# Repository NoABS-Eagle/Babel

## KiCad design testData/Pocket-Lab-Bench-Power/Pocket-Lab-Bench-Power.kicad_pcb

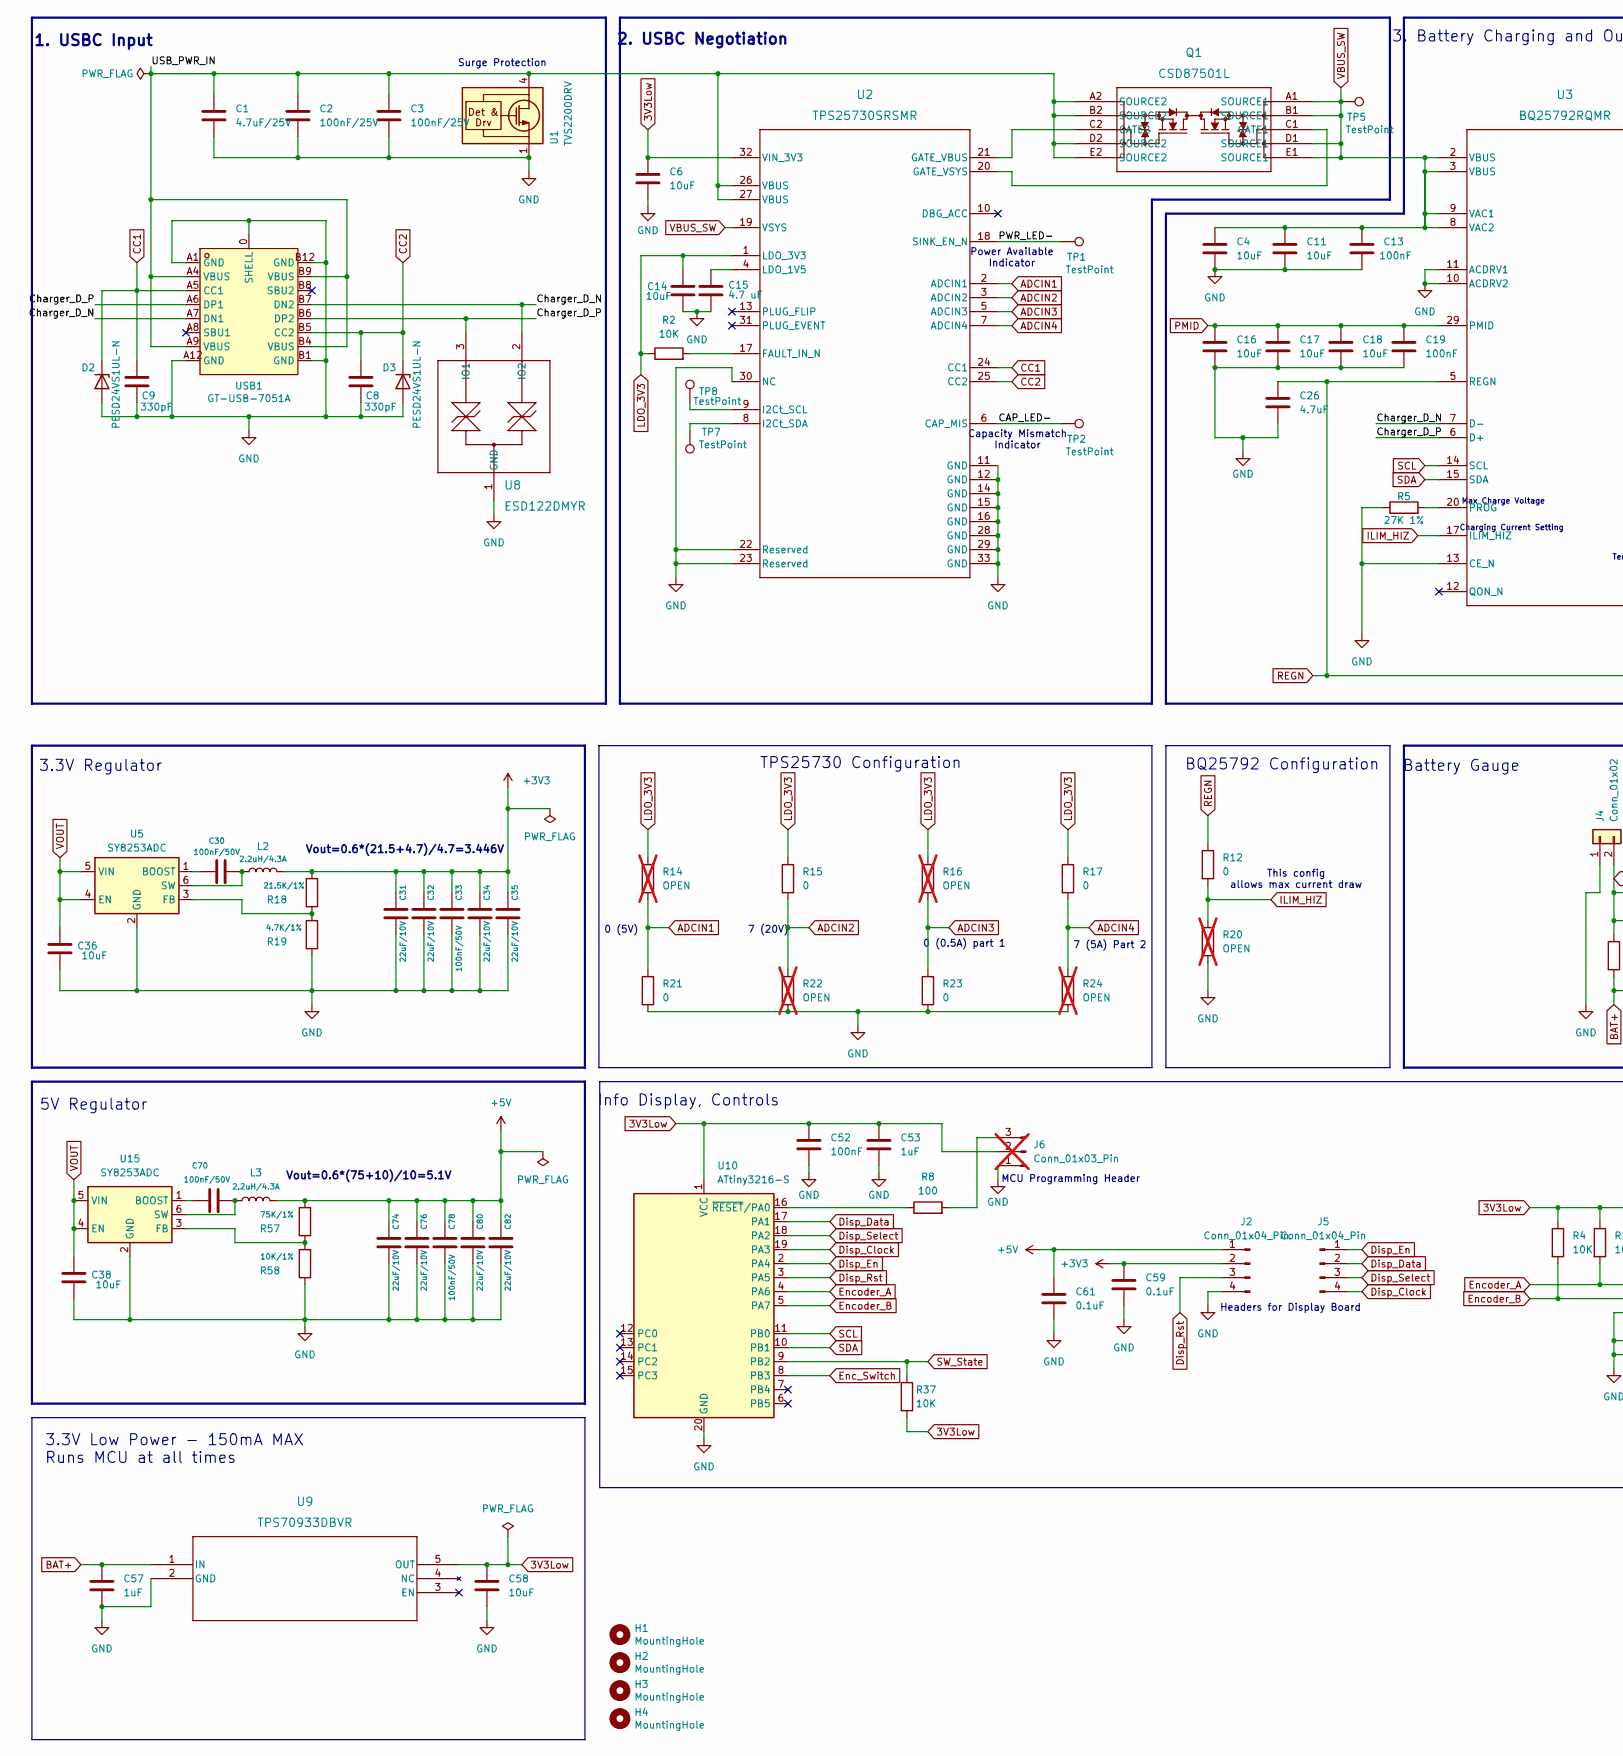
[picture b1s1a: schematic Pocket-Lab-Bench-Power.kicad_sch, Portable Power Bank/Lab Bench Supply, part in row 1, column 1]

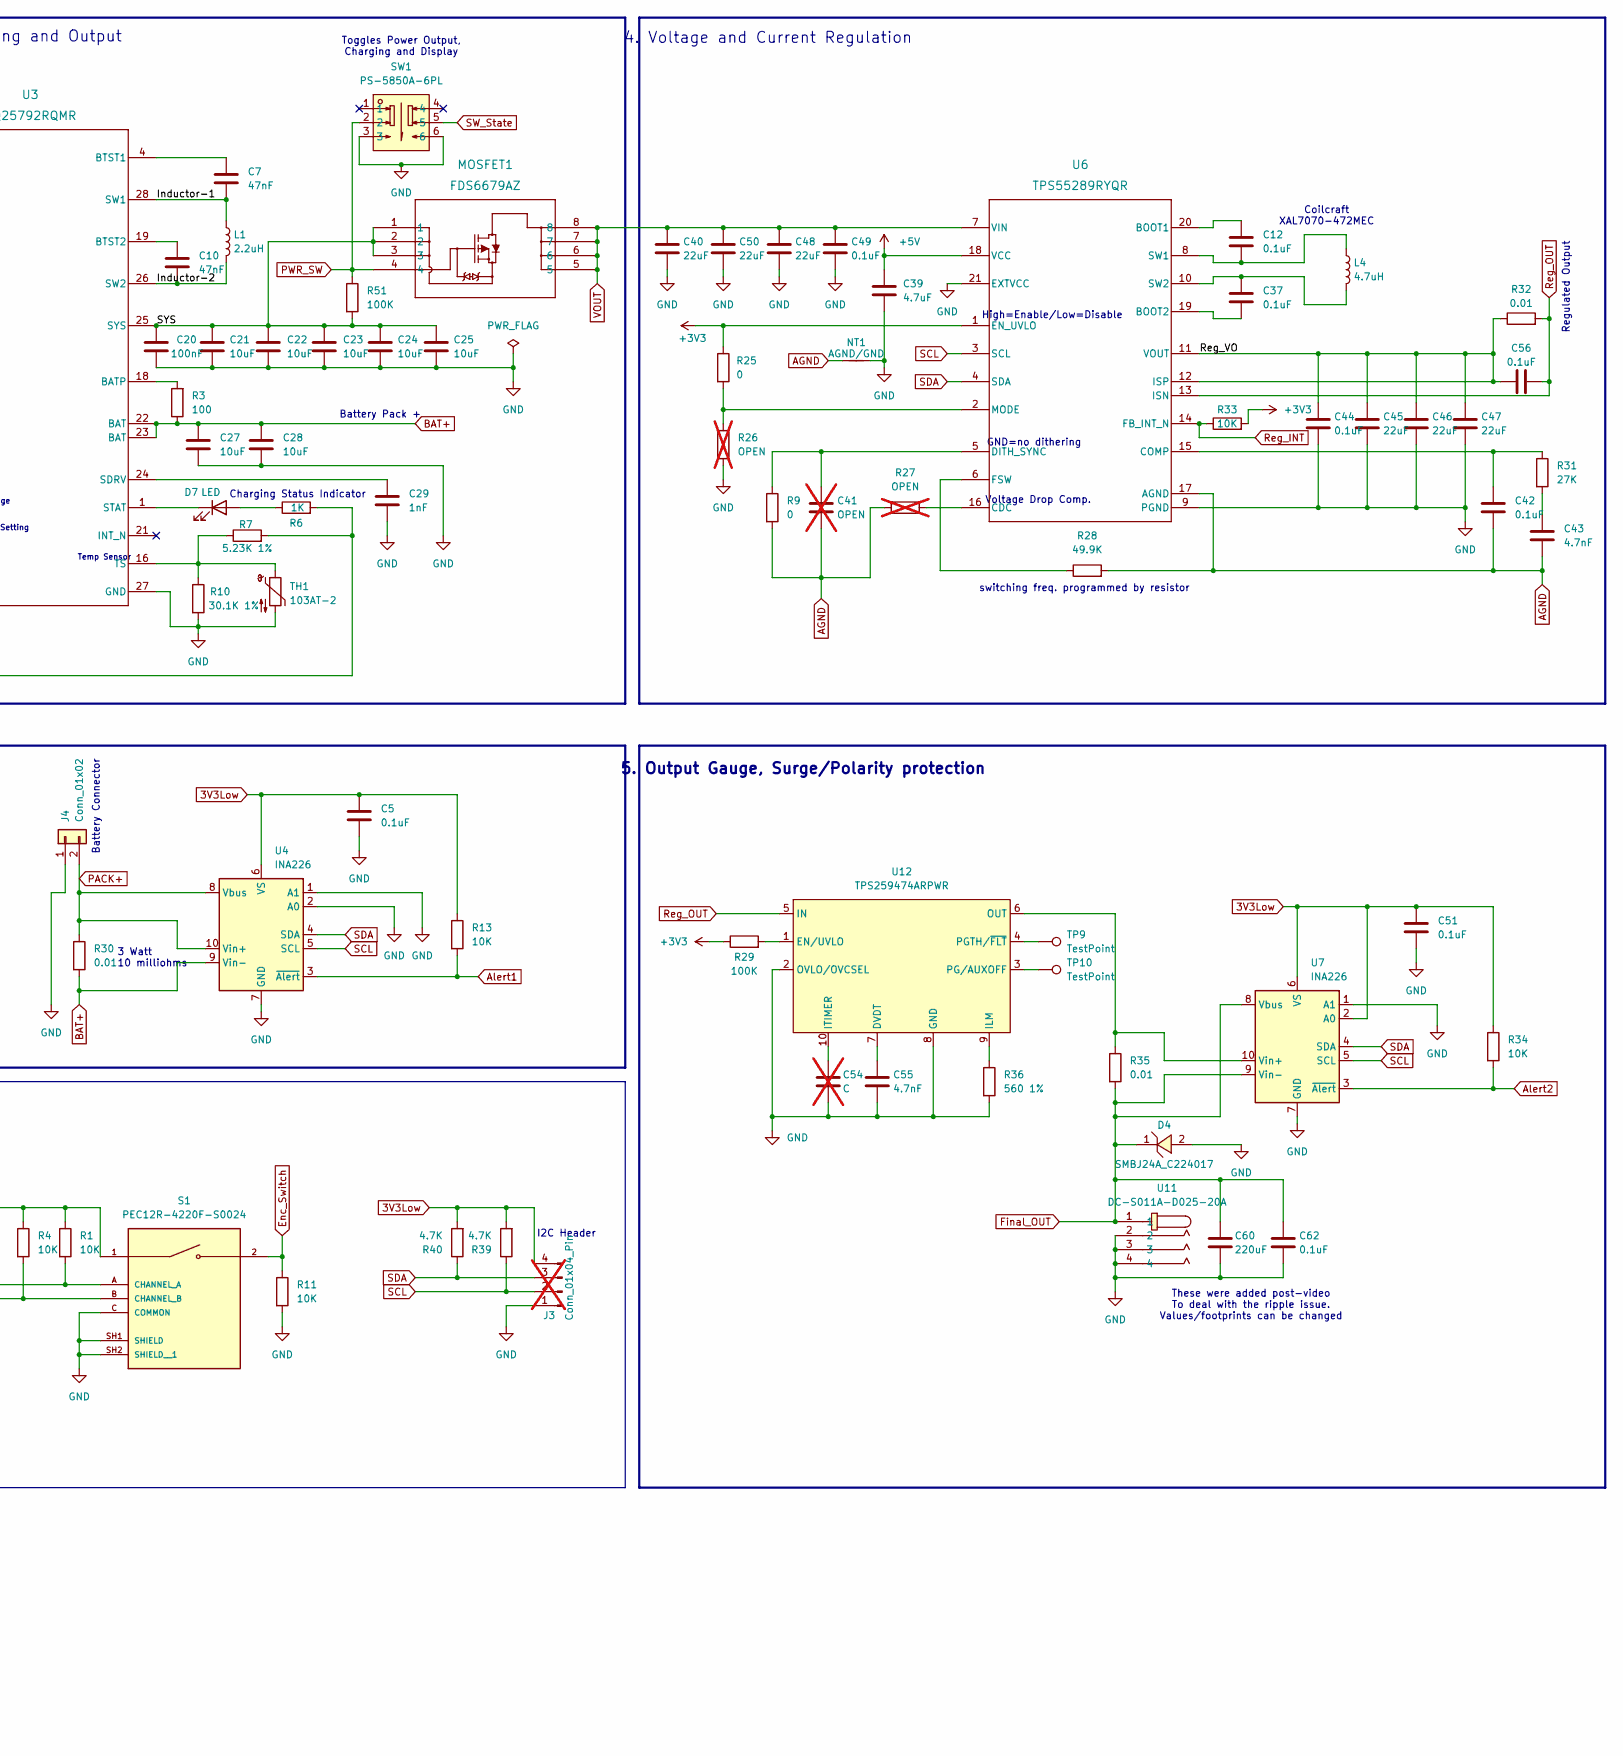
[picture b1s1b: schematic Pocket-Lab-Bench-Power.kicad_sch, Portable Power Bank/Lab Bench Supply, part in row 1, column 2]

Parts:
C1: 4.7uF/25V; C_0603_1608Metric
C2, C3: 100nF/25V; C_0603_1608Metric
C4, C11, C16, C17, C18, C21, C22, C23, C24, C25, C27, C28: 10uF; C_0805_2012Metric
C5, C12, C37, C42, C44, C49, C51, C56: 0.1uF; C_0402_1005Metric
C6, C14, C58: 10uF; C_0402_1005Metric
C7, C10: 47nF; C_0402_1005Metric
C8, C9: 330pF; C_0402_1005Metric
C13, C19, C20, C52: 100nF; C_0402_1005Metric
C15: 4.7 uF; C_0402_1005Metric
C26: 4.7uF; C_0603_1608Metric; Voltage Req 10V
C29: 1nF; C_0402_1005Metric
C30, C33, C70, C78: 100nF/50V; C_0603_1608Metric
C31, C32, C34, C35, C74, C76, C80, C82: 22uF/10V; C_0603_1608Metric
C36, C38: 10uF; C_0603_1608Metric
C39: 4.7uF; C_0603_1608Metric
C40, C45, C46, C47, C48, C50: 22uF; C_0603_1608Metric
C41: OPEN; C_0603_1608Metric; not fitted
C43: 4.7nF; C_0402_1005Metric
C53: 1uF; C_0402_1005Metric
C54: C; C_0603_1608Metric; not fitted
C55: 4.7nF; C_0603_1608Metric
C57: 1uF; C_0603_1608Metric
C59, C61, C62: 0.1uF; C_0603_1608Metric
C60: 220uF; C_0805_2012Metric
D2, D3: PESD24VS1UL-N; DFN1006-2L-RD; LCSC Part C406227
D4: SMBJ24A_C224017; SMB_L4.3-W3.6-LS5.4-RD; MPN SMBJ24A; LCSC Part C224017
D7: LED; LED_0603_1608Metric; LCSC Part C72038
H1, H2, H3, H4: MountingHole; MountingHole_3.2mm_M3
J2, J5: Conn_01x04_Pin; PinHeader_1x04_P2.54mm_Vertical; LCSC Part C2691448
J3: Conn_01x04_Pin; PinHeader_1x04_P2.54mm_Vertical; LCSC Part C2691448; not fitted
J4: Conn_01x02; JST_XH_B2B-XH-A_1x02_P2.50mm_Vertical; LCSC Part C495685
J6: Conn_01x03_Pin; PinHeader_1x03_P2.54mm_Vertical; LCSC Part C42431836; not fitted
L1: 2.2uH; IND-SMD_L7.0-W6.6_MCW-0650-220; LCSC Part C5349701
L2, L3: 2.2uH/4.3A; L_Sunlord_SWPA4020S; LCSC Part C3222957
L4: 4.7uH; IND-SMD_L7.5-W7.2-1; LCSC Part C3911513
MOSFET1: FDS6679AZ; SOIC8_751EB_ONS; LCSC Part C116730
NT1: AGND/GND; NetTie-2_SMD_Pad0.5mm
Q1: CSD87501L; PICOSTAR-YJG_TEX; LCSC Part C2841784
R1, R4, R11: 10K; R_0603_1608Metric
R2, R13, R33, R34, R37: 10K; R_0402_1005Metric
R3, R8: 100; R_0603_1608Metric
R5: 27K 1%; R_0603_1608Metric
R6: 1K; R_0603_1608Metric
R7: 5.23K 1%; R_0603_1608Metric
R9, R12, R15, R17, R21, R23, R25: 0; R_0603_1608Metric
R10: 30.1K 1%; R_0603_1608Metric
R14, R16, R20, R22, R24, R26, R27: OPEN; R_0603_1608Metric; not fitted
R18: 21.5K/1%; R_0603_1608Metric
R19: 4.7K/1%; R_0603_1608Metric
R28: 49.9K; R_0603_1608Metric
R29, R51: 100K; R_0603_1608Metric
R30, R32, R35: 0.01; R_2512_6332Metric; LCSC Part C840621
R31: 27K; R_0402_1005Metric
R36: 560 1%; R_0603_1608Metric
R39, R40: 4.7K; R_0603_1608Metric
R57: 75K/1%; R_0603_1608Metric
R58: 10K/1%; R_0603_1608Metric
S1: PEC12R-4220F-S0024; XDCR_PEC12R-4220F-S0024; PARTREV 07/21; LCSC Part C18164805
SW1: PS-5850A-6PL; SW-TH_6P-L5.8-W5.8-P2.00-LS4.5-BL_1; MPN PS-5850A-6PL; LCSC Part C963201
TH1: 103AT-2; PinHeader_1x02_P2.54mm_Vertical
TP1, TP2, TP5, TP7, TP8, TP9, TP10: TestPoint; TestPoint_Pad_D1.5mm
U1: TVS2200DRV; WSON-6-1EP_2x2mm_P0.65mm_EP1x1.6mm; LCSC Part C523793
U2: TPS25730SRSMR; RSM0032B-IPC_A; LCSC Part C22390380
U3: BQ25792RQMR; BQ25792; LCSC Part C2862876
U4: INA226; VSSOP-10_3x3mm_P0.5mm
U5, U15: SY8253ADC; TSOT-23-6; LCSC Part C93736
U6: TPS55289RYQR; RYQ0021A-MFG; LCSC Part C5942077
U7: INA226; VSSOP-10_3x3mm_P0.5mm; LCSC Part C49851
U8: ESD122DMYR; DMY0003A; LCSC Part C1975871
U9: TPS70933DBVR; DBV5_TEX; LCSC Part C89347
U10: ATtiny3216-S; SOIC-20W_7.5x12.8mm_P1.27mm; LCSC Part C1340355
U11: DC-S011A-D025-20A; AUDIO-TH_DC-S011A-D025-20A; MPN DC-S011A-D025-20A; LCSC Part C7464915
U12: TPS259474ARPWR; VQFN-10_L2.0-W2.0-P0.45-TL; MPN TPS259474ARPWR; LCSC Part C3662807
USB1: GT-USB-7051A; USB-C-SMD_GT-USB-7051A; MPN GT-USB-7051A; LCSC Part C2843970

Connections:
3V3Low: C5.1, C6.1, C51.1, C52.1, C53.1, C58.1, J3.4, J6.2, R1.1, R4.1, R13.1, R34.1, R37.2, R39.2, R40.2, S1.1, U2.32 (VIN_3V3), U4.6 (VS), U7.2 (A0), U7.6 (VS), U9.5 (OUT), U10.1 (VCC)
+3V3: C31.2, C32.2, C33.1, C34.2, C35.2, C59.1, J2.2, L2.2, R18.2, R25.1, R29.1, R33.2, U6.1 (EN_UVLO)
+5V: C39.1, C61.1, C74.2, C76.2, C78.1, C80.2, C82.2, J2.1, L3.2, R57.2, U6.18 (VCC)
/CAP_LED-: TP2.1, U2.6 (CAP_MIS)
/Charger_D_N: U3.7 (D-), U8.2 (IO2), USB1.A7 (DN1), USB1.B7 (DN2)
/Charger_D_P: U3.6 (D+), U8.3 (IO1), USB1.A6 (DP1), USB1.B6 (DP2)
/Inductor-1: C7.2, L1.1, U3.28 (SW1)
/Inductor-2: C10.2, L1.2, U3.26 (SW2)
/PWR_LED-: TP1.1, U2.18 (SINK_EN_N)
/Reg_VO: C44.1, C45.1, C46.1, C47.1, C56.1, R32.1, U6.11 (VOUT), U6.12 (ISP)
/SYS: C20.1, C21.1, C22.1, C23.1, C24.1, C25.1, MOSFET1.1, MOSFET1.2, MOSFET1.3, R51.2, U3.25 (SYS)
/USB_PWR_IN: C1.1, C2.1, C3.1, Q1.A2 (SOURCE2), Q1.B2 (SOURCE2), Q1.D2 (SOURCE2), Q1.E2 (SOURCE2), U1.4 (IN), U1.5 (IN), U1.6 (IN), U2.26 (VBUS), U2.27 (VBUS), USB1.A4 (VBUS), USB1.A9 (VBUS), USB1.B4 (VBUS), USB1.B9 (VBUS)
ADCIN1: R14.2, R21.1, U2.2 (ADCIN1)
ADCIN2: R15.2, R22.1, U2.3 (ADCIN2)
ADCIN3: R16.2, R23.1, U2.5 (ADCIN3)
ADCIN4: R17.2, R24.1, U2.7 (ADCIN4)
AGND: C41.2, C42.2, C43.2, NT1.1, R9.2, R27.1, R28.2, U6.17 (AGND)
Alert1: R13.2, U4.3 (~Alert)
Alert2: R34.2, U7.3 (~Alert)
BAT+: C27.1, C28.1, C57.1, R3.1, R30.2, U3.22 (BAT), U3.23 (BAT), U4.9 (Vin-), U9.1 (IN)
CC1: C9.1, D2.1 (K), U2.24 (CC1), USB1.A5 (CC1)
CC2: C8.1, D3.1 (K), U2.25 (CC2), USB1.B5 (CC2)
Disp_Clock: J5.4, U10.19 (PA3)
Disp_Data: J5.2, U10.17 (PA1)
Disp_En: J5.1, U10.2 (PA4)
Disp_Rst: J2.3, U10.3 (PA5)
Disp_Select: J5.3, U10.18 (PA2)
Enc_Switch: R11.1, S1.2, U10.8 (PB3)
Encoder_A: R1.2, S1.A (CHANNEL_A), U10.4 (PA6)
Encoder_B: R4.2, S1.B (CHANNEL_B), U10.5 (PA7)
Final_OUT: C60.1, C62.1, D4.1, R35.2, U7.8 (Vbus), U7.9 (Vin-), U11.1
GND: C1.2, C2.2, C3.2, C4.1, C5.2, C6.2, C8.2, C9.2, C11.1, C13.2, C14.2, C15.2, C16.2, C17.2, C18.1, C19.2, C20.2, C21.2, C22.2, C23.2, C24.2, C25.2, C26.2, C27.2, C28.2, C29.2, C31.1, C32.1, C33.2, C34.1, C35.1, C36.2, C38.2, C39.2, C40.2, C44.2, C45.2, C46.2, C47.2, C48.2, C49.2, C50.2, C51.2, C52.2, C53.2, C54.2, C55.2, C57.2, C58.2, C59.2, C60.2, C61.2, C62.2, C74.1, C76.1, C78.2, C80.1, C82.1, D2.2 (A), D3.2 (A), D4.2, J2.4, J3.1, J4.1, J6.1, NT1.2, R5.1, R10.2, R11.2, R19.1, R20.2, R21.2, R22.2, R23.2, R24.2, R26.2, R36.2, R58.1, S1.C (COMMON), S1.SH1 (SHIELD), S1.SH2 (SHIELD__1), SW1.3, SW1.6, TH1.2, U1.1 (GND), U1.2 (GND), U1.3 (GND), U1.7 (GND), U2.11 (GND), U2.12 (GND), U2.14 (GND), U2.15 (GND), U2.16 (GND), U2.22 (Reserved), U2.23 (Reserved), U2.28 (GND), U2.29 (GND), U2.30 (NC), U2.33 (GND), U3.10 (ACDRV2), U3.11 (ACDRV1), U3.13 (CE_N), U3.27 (GND), U4.1 (A1), U4.2 (A0), U4.7 (GND), U5.2 (GND), U6.9 (PGND), U6.21 (EXTVCC), U7.1 (A1), U7.7 (GND), U8.1 (GND), U9.2 (GND), U10.20 (GND), U11.2, U11.3, U11.4, U12.2 (OVLO/OVCSEL), U12.8 (GND), U15.2 (GND), USB1.0 (SHELL), USB1.A1 (GND), USB1.A12 (GND), USB1.B1 (GND), USB1.B12 (GND)
ILIM_HIZ: R12.2, R20.1, U3.17 (ILIM_HIZ)
LDO_3V3: C14.1, R2.1, R14.1, R15.1, R16.1, R17.1, U2.1 (LDO_3V3)
unnamed: C43.1, R31.2
unnamed: D7.2 (A), R6.1
unnamed: D7.1 (K), U3.1 (STAT)
unnamed: J6.3, R8.2
unnamed: Q1.C1 (GATE1), U2.20 (GATE_VSYS)
unnamed: Q1.C2 (GATE2), U2.21 (GATE_VBUS)
unnamed: R2.2, U2.17 (FAULT_IN_N)
unnamed: TP8.1, U2.9 (I2Ct_SCL)
unnamed: TP7.1, U2.8 (I2Ct_SDA)
unnamed: C15.1, U2.4 (LDO_1V5)
unnamed: R3.2, U3.18 (BATP)
unnamed: C7.1, U3.4 (BTST1)
unnamed: C10.1, U3.19 (BTST2)
unnamed: R5.2, U3.20 (PROG)
unnamed: C29.1, U3.24 (SDRV)
unnamed: R7.1, R10.1, TH1.1, U3.16 (TS)
unnamed: C30.2, U5.1 (BOOST)
unnamed: R18.1, R19.2, U5.3 (FB)
unnamed: C30.1, L2.1, U5.6 (SW)
unnamed: C12.1, U6.20 (BOOT1)
unnamed: C37.2, U6.19 (BOOT2)
unnamed: R27.2, U6.16 (CDC)
unnamed: C42.1, R31.1, U6.15 (COMP)
unnamed: C41.1, R9.1, U6.5 (DITH_SYNC)
unnamed: R28.1, U6.6 (FSW)
unnamed: R25.2, R26.1, U6.2 (MODE)
unnamed: C12.2, L4.1, U6.8 (SW1)
unnamed: C37.1, L4.2, U6.10 (SW2)
unnamed: R8.1, U10.16 (~RESET/PA0)
unnamed: C55.1, U12.7 (DVDT)
unnamed: R29.2, U12.1 (EN/UVLO)
unnamed: R36.1, U12.9 (ILM)
unnamed: C54.1, U12.10 (ITIMER)
unnamed: R35.1, U7.10 (Vin+), U12.6 (OUT)
unnamed: TP9.1, U12.4 (PGTH/~FLT)
unnamed: TP10.1, U12.3 (PG/AUXOFF)
unnamed: C70.2, U15.1 (BOOST)
unnamed: R57.1, R58.2, U15.3 (FB)
unnamed: C70.1, L3.1, U15.6 (SW)
PACK+: J4.2, R30.1, U4.8 (Vbus), U4.10 (Vin+)
PMID: C16.1, C17.1, C18.2, C19.1, U3.29 (PMID)
PWR_SW: MOSFET1.4, R51.1, SW1.2
REGN: C26.1, R6.2, R7.2, R12.1, U3.5 (REGN)
Reg_INT: R33.1, U6.14 (FB_INT_N)
Reg_OUT: C56.2, R32.2, U6.13 (ISN), U12.5 (IN)
SCL: J3.2, R39.1, U3.14 (SCL), U4.5 (SCL), U6.3 (SCL), U7.5 (SCL), U10.11 (PB0)
SDA: J3.3, R40.1, U3.15 (SDA), U4.4 (SDA), U6.4 (SDA), U7.4 (SDA), U10.10 (PB1)
SW_State: R37.1, SW1.5, U10.9 (PB2)
VBUS_SW: C4.2, C11.2, C13.1, Q1.A1 (SOURCE1), Q1.B1 (SOURCE1), Q1.D1 (SOURCE1), Q1.E1 (SOURCE1), TP5.1, U2.19 (VSYS), U3.2 (VBUS), U3.3 (VBUS), U3.8 (VAC2), U3.9 (VAC1)
VOUT: C36.1, C38.1, C40.1, C48.1, C49.1, C50.1, MOSFET1.5, MOSFET1.6, MOSFET1.7, MOSFET1.8, U5.4 (EN), U5.5 (VIN), U6.7 (VIN), U15.4 (EN), U15.5 (VIN)

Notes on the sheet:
Info Display, Controls
GND=no dithering
Battery Connector
4. Voltage and Current Regulation
Surge Protection
Voltage Drop Comp.
0 (5V)
switching freq. programmed by resistor
Battery Pack +
Charging Status Indicator
7 (20V)
BQ25792 Configuration
I2C Header
Temp Sensor
3.3V Regulator
Headers for Display Board
Coilcraft XAL7070-472MEC
1. USBC Input
2. USBC Negotiation
TPS25730 Configuration
5. Output Gauge, Surge/Polarity protection
Regulated Output
3.3V Low Power - 150mA MAX Runs MCU at all times
3. Battery Charging and Output
7 (5A) Part 2
0 (0.5A) part 1
Capacity Mismatch Indicator
Charging Current Setting
These were added post-video To deal with the ripple issue. Values/footprints can be changed
Power Available Indicator
MCU Programming Header
This config allows max current draw
Toggles Power Output, Charging and Display
3 Watt 10 milliohms
Max Charge Voltage
5V Regulator
Vout=0.6*(21.5+4.7)/4.7=3.446V
High=Enable/Low=Disable
Battery Gauge
Vout=0.6*(75+10)/10=5.1V

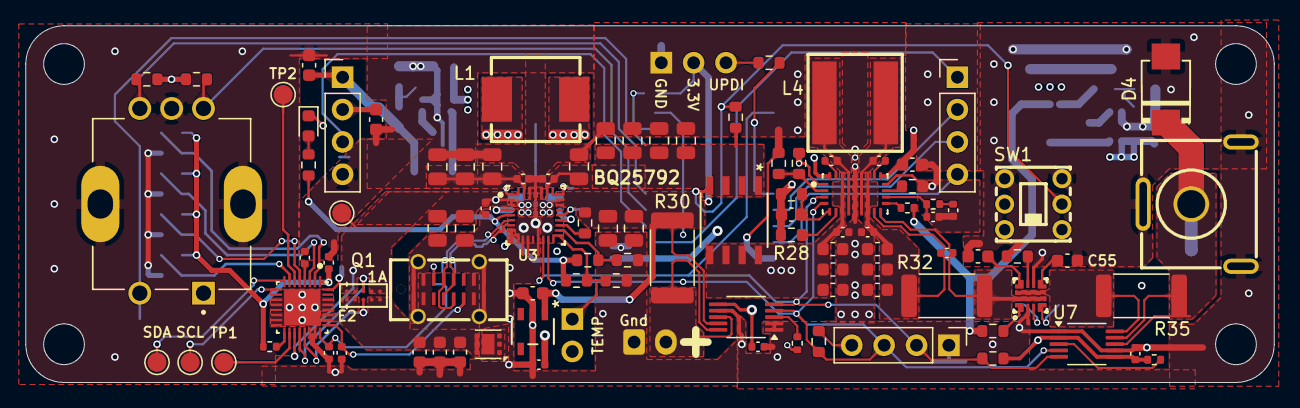
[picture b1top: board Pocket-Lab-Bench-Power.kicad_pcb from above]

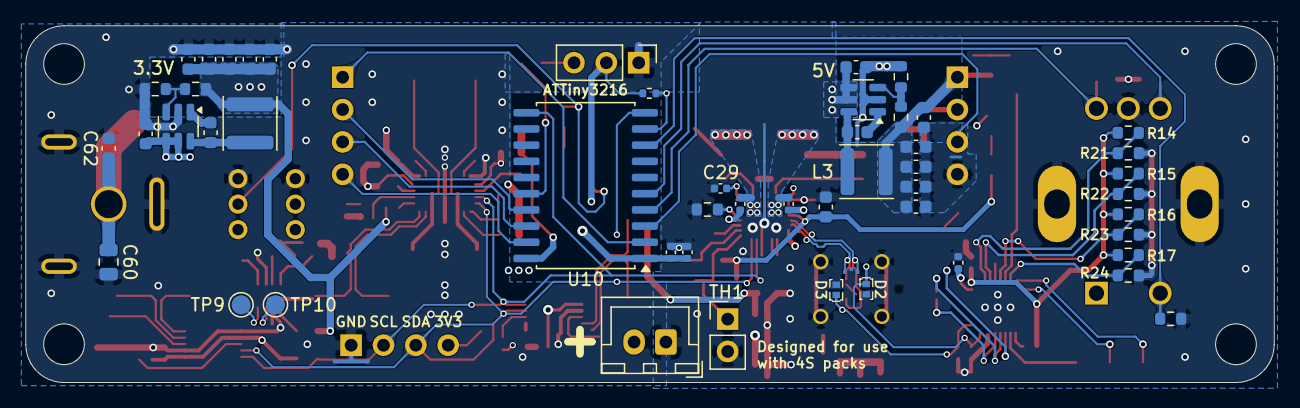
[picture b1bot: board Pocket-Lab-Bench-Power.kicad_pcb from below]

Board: 4 copper layers, 98.0 x 28.0 mm, 154 parts (51 on the bottom side), 84 nets.

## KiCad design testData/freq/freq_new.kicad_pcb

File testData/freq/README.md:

# Частотник для ООО «Ирбис», ревизия с абсолютным энкодером

## Аппаратная часть:
  * STM32F302RBT6
  * Входы/выходы:
    * Силовые:
      * Вход питания, 2 клеммы
      * Двигатель, 3 клеммы
      * Выход на лампу-строб, 2 клеммы
    * Слаботочные:
      * Пост внутренний, 4 клеммы
      * Пост внешний, 4 клеммы
      * Радар внутренний, 4 клеммы
      * Радар внешний, 4 клеммы
      * ДЗК, 2 клеммы
      * Световая завеса (они же — фотодатчики), 4 клеммы
      * Радиуправление, 4 клеммы
      * Внутренняя магнитная петля, 4 клеммы
      * Внешняя магнитная петля, 4 клеммы
      * Замок, 2 клеммы
      * 485 для энкодера — 4 клеммы
      * 485 для чего-то ещё — 4 клеммы
  * Шунт для ограничения максимального тока через движок, LRP12FTDRR020
  * Двухэтажные клеммники:
    * DG127A-5.08-06P-14-00AH
    * DG127A-5.08-04P-14-00AH

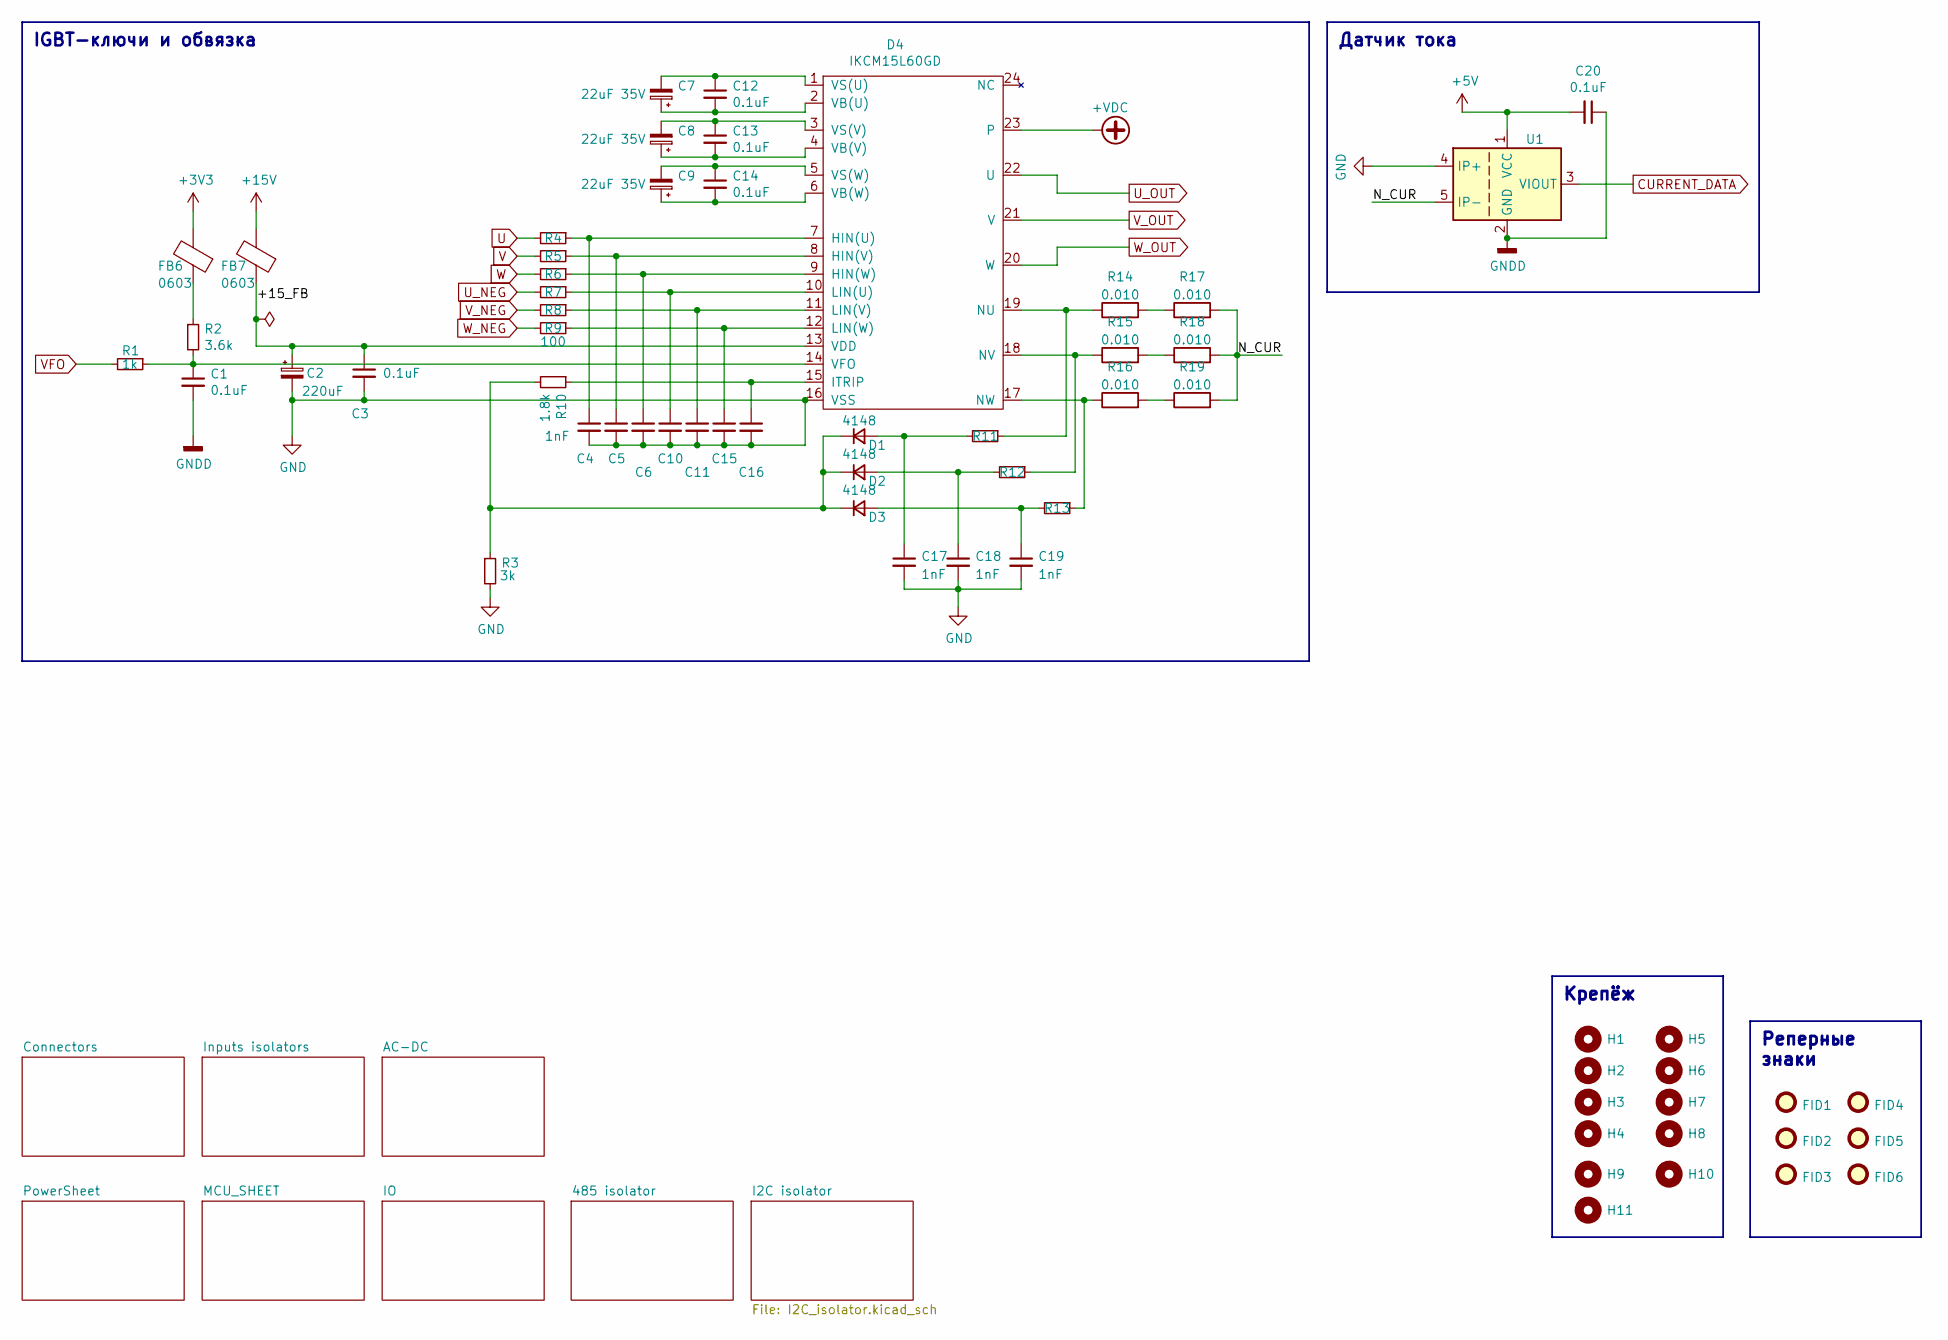
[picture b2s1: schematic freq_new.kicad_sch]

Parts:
C1, C3, C12, C13, C14, C20: 0.1uF; C_0603_1608Metric
C2: 220uF; CP_Elec_8x10.5
C4, C5, C6, C10, C11, C15, C16, C17, C18, C19: 1nF; C_0603_1608Metric
C7, C8, C9: 22uF 35V; CP_Elec_6.3x5.2
D1, D2, D3: 4148; D_SOD-123
D4: IKCM15L60GD; INF-CIPOS_MINI
FB6, FB7: 0603; R_0603_1608Metric
FID1, FID2, FID3, FID4, FID5, FID6: Fiducial; Fiducial_1.5mm_Mask4.5mm
H1, H2, H3, H4, H5, H6, H7, H8, H9, H10, H11: MountingHole-Mechanical; MountingHole_3.2mm_M3_ISO7380_Pad
R1: 1k; R_0603_1608Metric
R2: 3.6k; R_0603_1608Metric
R3: 3k; R_0603_1608Metric
R4, R5, R6, R7, R8, R9, R11, R12, R13: 100; R_0603_1608Metric
R10: 1.8k; R_0603_1608Metric
R14, R15, R16, R17, R18, R19: 0.010; R_2512_6332Metric
U1: ACS758xCB-050B-PFF; Allegro_CB_PFF

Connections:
+3V3: FB6.2; also elsewhere on the board
+5V: C20.2, U1.1 (VCC); also elsewhere on the board
+15V: FB7.2; also elsewhere on the board
+VDC: D4.23; also elsewhere on the board
/+15_FB: C2.1, C3.1, D4.13 (VDD), FB7.1
/N_CUR: R17.2, R18.2, R19.2, U1.5 (IP-)
CURRENT_DATA: U1.3 (VIOUT); also elsewhere on the board
GND: C2.2, C3.2, C4.2, C5.2, C6.2, C10.2, C11.2, C15.2, C16.2, C17.2, C18.2, C19.2, D4.16 (VSS), R3.2, U1.4 (IP+); also elsewhere on the board
GNDD: C1.2, C20.1, U1.2 (GND); also elsewhere on the board
unnamed: C17.1, D1.2 (A), R11.2
unnamed: D1.1 (K), D2.1 (K), D3.1 (K), R3.1, R10.2
unnamed: C18.1, D2.2 (A), R12.2
unnamed: C19.1, D3.2 (A), R13.2
unnamed: C4.1, D4.7 (HIN(U)), R4.1
unnamed: C5.1, D4.8 (HIN(V)), R5.1
unnamed: C6.1, D4.9 (HIN(W)), R6.1
unnamed: C16.1, D4.15 (ITRIP), R10.1
unnamed: C10.1, D4.10 (LIN(U)), R7.1
unnamed: C11.1, D4.11 (LIN(V)), R8.1
unnamed: C15.1, D4.12 (LIN(W)), R9.1
unnamed: D4.19 (NU), R11.1, R14.1
unnamed: D4.18 (NV), R12.1, R15.1
unnamed: D4.17 (NW), R13.1, R16.1
unnamed: C7.1, C12.2, D4.2 (VB(U))
unnamed: C8.1, C13.2, D4.4 (VB(V))
unnamed: C9.1, C14.2, D4.6 (VB(W))
unnamed: C1.1, D4.14 (VFO), R1.1, R2.2
unnamed: C7.2, C12.1, D4.1 (VS(U))
unnamed: C8.2, C13.1, D4.3 (VS(V))
unnamed: C9.2, C14.1, D4.5 (VS(W))
unnamed: FB6.1, R2.1
unnamed: R14.2, R17.1
unnamed: R15.2, R18.1
unnamed: R16.2, R19.1
U: R4.2; also elsewhere on the board
U_NEG: R7.2; also elsewhere on the board
U_OUT: D4.22 (U); also elsewhere on the board
V: R5.2; also elsewhere on the board
VFO: R1.2; also elsewhere on the board
V_NEG: R8.2; also elsewhere on the board
V_OUT: D4.21 (V); also elsewhere on the board
W: R6.2; also elsewhere on the board
W_NEG: R9.2; also elsewhere on the board
W_OUT: D4.20 (W); also elsewhere on the board

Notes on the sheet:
Реперные знаки
IGBT-ключи и обвязка
Датчик тока
Крепёж

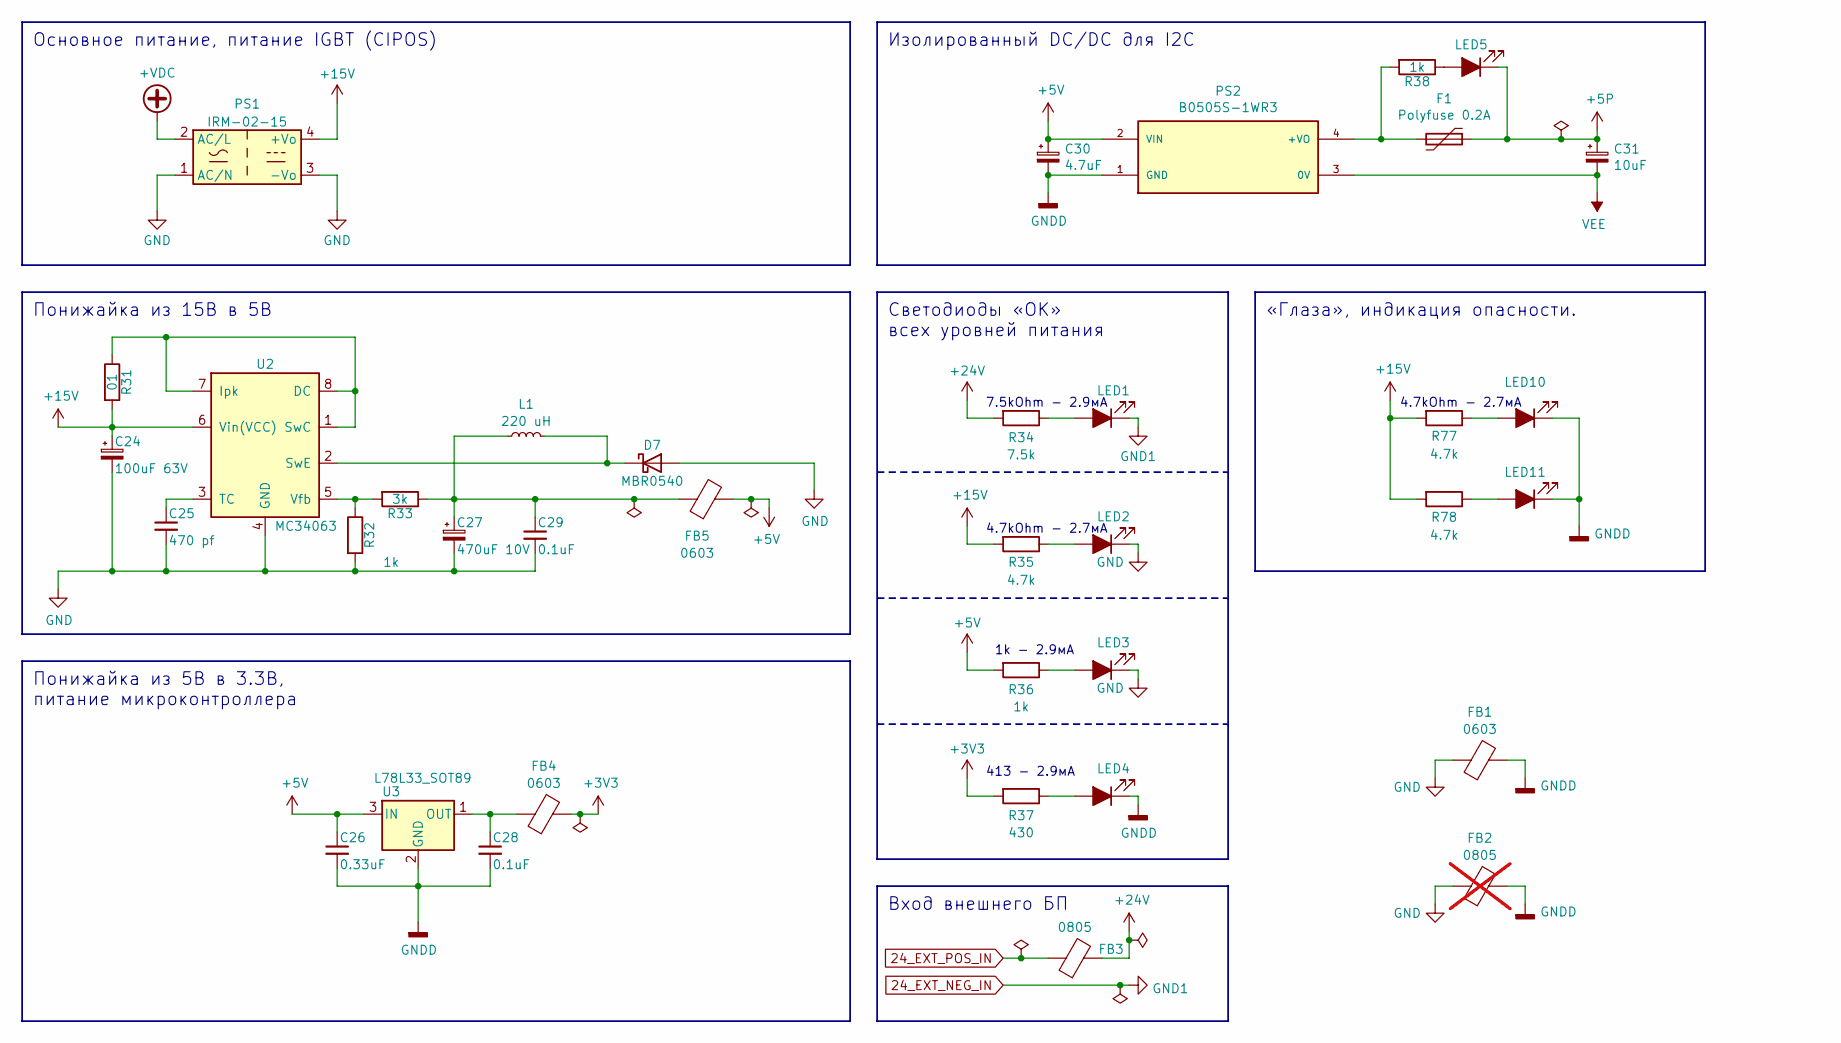
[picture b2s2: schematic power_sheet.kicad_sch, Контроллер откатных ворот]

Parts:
C24: 100uF 63V; CP_Elec_8x10.5
C25: 470 pf; C_0603_1608Metric
C26: 0.33uF; C_0805_2012Metric
C27: 470uF 10V; CP_Elec_8x10
C28, C29: 0.1uF; C_0603_1608Metric
C30: 4.7uF; CP_Elec_4x5.3
C31: 10uF; CP_Elec_4x5.3
D7: MBR0540; D_SOD-123
F1: Polyfuse 0.2A; Fuse_1812_4532Metric
FB1, FB4, FB5: 0603; R_0603_1608Metric
FB2: 0805; R_0805_2012Metric; not fitted
FB3: 0805; R_0805_2012Metric
L1: 220 uH; SWPA6045S221MT
LED1, LED2, LED3, LED4: LED_ORANGE; LED_0603_1608Metric
LED5, LED10, LED11: LED_RED; LED_0603_1608Metric
PS1: IRM-02-15; Converter_ACDC_MeanWell_IRM-02-xx_THT
PS2: B0505S-1WR3; CONV_B0505S-1WR3; PARTREV 2018.06.29-A/2
R31: 01; R_0805_2012Metric
R32, R36, R38: 1k; R_0603_1608Metric
R33: 3k; R_0603_1608Metric
R34: 7.5k; R_0603_1608Metric
R35, R77, R78: 4.7k; R_0603_1608Metric
R37: 430; R_0603_1608Metric
U2: MC34063; SOIC-8_3.9x4.9mm_P1.27mm
U3: L78L33_SOT89; SOT-89-3

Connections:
24_EXT_NEG_IN: LED1.1 (K); also elsewhere on the board
24_EXT_POS_IN: FB3.1; also elsewhere on the board
+3V3: FB4.2, R37.2; also elsewhere on the board
+5P: C31.1, F1.1, LED5.1 (K); also elsewhere on the board
+5V: C26.1, C30.1, FB5.2, PS2.2 (VIN), R36.2, U3.3 (IN); also elsewhere on the board
+15V: C24.1, PS1.4 (+Vo), R31.2, R35.2, R77.2, R78.2, U2.6 (Vin(VCC)); also elsewhere on the board
+24V: FB3.2, R34.2; also elsewhere on the board
+VDC: PS1.2 (AC/L); also elsewhere on the board
GND: C24.2, C25.2, C27.2, C29.2, D7.2 (A), FB1.1, FB2.1, LED2.1 (K), LED3.1 (K), PS1.1 (AC/N), PS1.3 (-Vo), R32.2, U2.4 (GND); also elsewhere on the board
GNDD: C26.2, C28.2, C30.2, FB1.2, FB2.2, LED4.1 (K), LED10.1 (K), LED11.1 (K), PS2.1 (GND), U3.2 (GND); also elsewhere on the board
unnamed: C27.1, C29.1, FB5.1, L1.1, R33.1
unnamed: D7.1 (K), L1.2, U2.2 (SwE)
unnamed: LED1.2 (A), R34.1
unnamed: LED2.2 (A), R35.1
unnamed: LED3.2 (A), R36.1
unnamed: LED4.2 (A), R37.1
unnamed: LED5.2 (A), R38.1
unnamed: LED10.2 (A), R77.1
unnamed: LED11.2 (A), R78.1
unnamed: F1.2, PS2.4 (+VO), R38.2
unnamed: R31.1, U2.1 (SwC), U2.7 (Ipk), U2.8 (DC)
unnamed: C25.1, U2.3 (TC)
unnamed: R32.1, R33.2, U2.5 (Vfb)
unnamed: C28.1, FB4.1, U3.1 (OUT)
VEE: C31.2, PS2.3 (0V); also elsewhere on the board

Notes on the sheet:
Светодиоды «ОК» всех уровней питания
Понижайка из 5В в 3.3В, питание микроконтроллера
«Глаза», индикация опасности.
Изолированный DC/DC для I2C
Основное питание, питание IGBT (CIPOS)
Вход внешнего БП
Понижайка из 15В в 5В
4.7kOhm - 2.7мА
7.5kOhm - 2.9мА
1k - 2.9мА
413 - 2.9мА

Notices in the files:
parts and their libraries:
Copyright 2021 Accelerated Designs. All rights reserved.
